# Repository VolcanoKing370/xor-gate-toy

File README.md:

# xor-gate-toy
This is a simple quad XOR gate (74HC86) that is controlled by 8 key switches and outputs to 4 LEDS, all powered by a coin cell battery. This is implemented in KiCAD.

# Why did you do this?
I wanted to challenge myself by designing a simple PCB without having to follow any YouTube tutorials. This means that I force myself to not copypasta whatever the tutorial did.

# Great. The PCB has already been designed... How do I get it manufactured!?
Coming soon!

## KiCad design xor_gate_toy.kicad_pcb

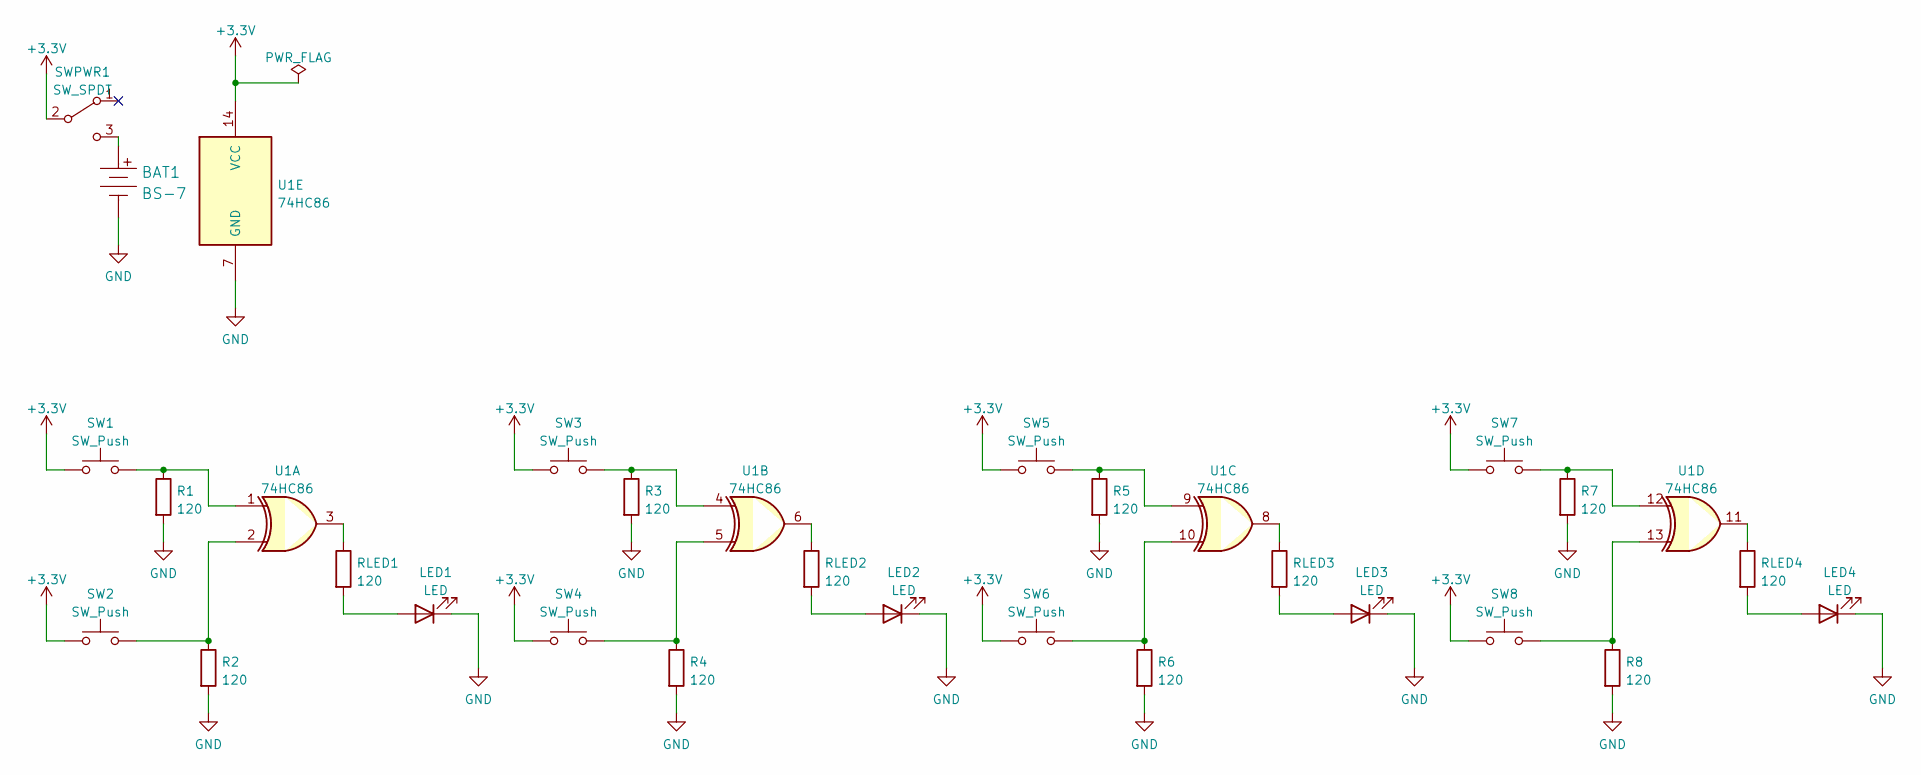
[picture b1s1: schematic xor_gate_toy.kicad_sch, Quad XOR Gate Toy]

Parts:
BAT1: BS-7; Battery_Holder_Coin_2032_BS-7; MPN BS-7; Digi-Key_PN BS-7-ND
LED1, LED2, LED3, LED4: LED; LED_D3.0mm
R1, R2, R3, R4, R5, R6, R7, R8: 120; R_Axial_DIN0207_L6.3mm_D2.5mm_P10.16mm_Horizontal
RLED1, RLED2, RLED3, RLED4: 120; R_Axial_DIN0207_L6.3mm_D2.5mm_P10.16mm_Horizontal
SW1, SW2, SW3, SW4, SW5, SW6, SW7, SW8: SW_Push; SW_Cherry_MX_PCB_1.00u
SWPWR1: SW_SPDT; Switch_Slide_11.6x4mm_EG1218
U1: 74HC86; DIP-14_W7.62mm

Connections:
+3.3V: SW1.1, SW2.1, SW3.1, SW4.1, SW5.1, SW6.1, SW7.1, SW8.1, SWPWR1.2 (B), U1.14 (VCC)
GND: BAT1.Neg, LED1.1 (K), LED2.1 (K), LED3.1 (K), LED4.1 (K), R1.2, R2.2, R3.2, R4.2, R5.2, R6.2, R7.2, R8.2, U1.7 (GND)
unnamed: BAT1.Pos, SWPWR1.3 (C)
unnamed: LED1.2 (A), RLED1.2
unnamed: LED2.2 (A), RLED2.2
unnamed: LED3.2 (A), RLED3.2
unnamed: LED4.2 (A), RLED4.2
unnamed: RLED1.1, U1.3
unnamed: RLED2.1, U1.6
unnamed: RLED3.1, U1.8
unnamed: RLED4.1, U1.11
unnamed: R1.1, SW1.2, U1.1
unnamed: R2.1, SW2.2, U1.2
unnamed: R3.1, SW3.2, U1.4
unnamed: R4.1, SW4.2, U1.5
unnamed: R5.1, SW5.2, U1.9
unnamed: R6.1, SW6.2, U1.10
unnamed: R7.1, SW7.2, U1.12
unnamed: R8.1, SW8.2, U1.13

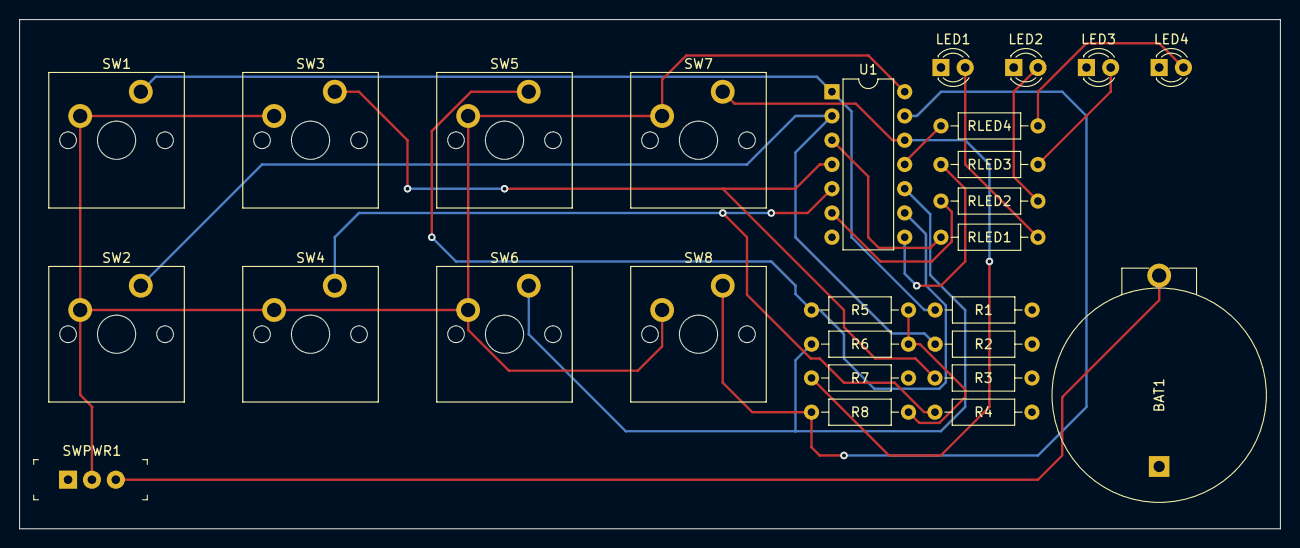
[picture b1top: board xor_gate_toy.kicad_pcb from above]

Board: 2 copper layers, 132.1 x 53.3 mm, 27 parts (0 on the bottom side), 19 nets.

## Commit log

2023-07-23 Added necessary files
    Not sure if this is needed, but I would highly recommend downloading the following footprint libraries:
    https://github.com/Digi-Key/digikey-kicad-library for the SPDT switch and coin cell battery holder.
    https://github.com/perigoso/keyswitch-kicad-library for the cherry switches.
2023-07-25 Add photos for README
    These screenshots demonstrate how to generate gerber and drill files
2023-07-25 Revert "Add photos for README"
    This reverts commit 62e0aefc57ab400c5ef3bb2293fb42c7fde9e540.
